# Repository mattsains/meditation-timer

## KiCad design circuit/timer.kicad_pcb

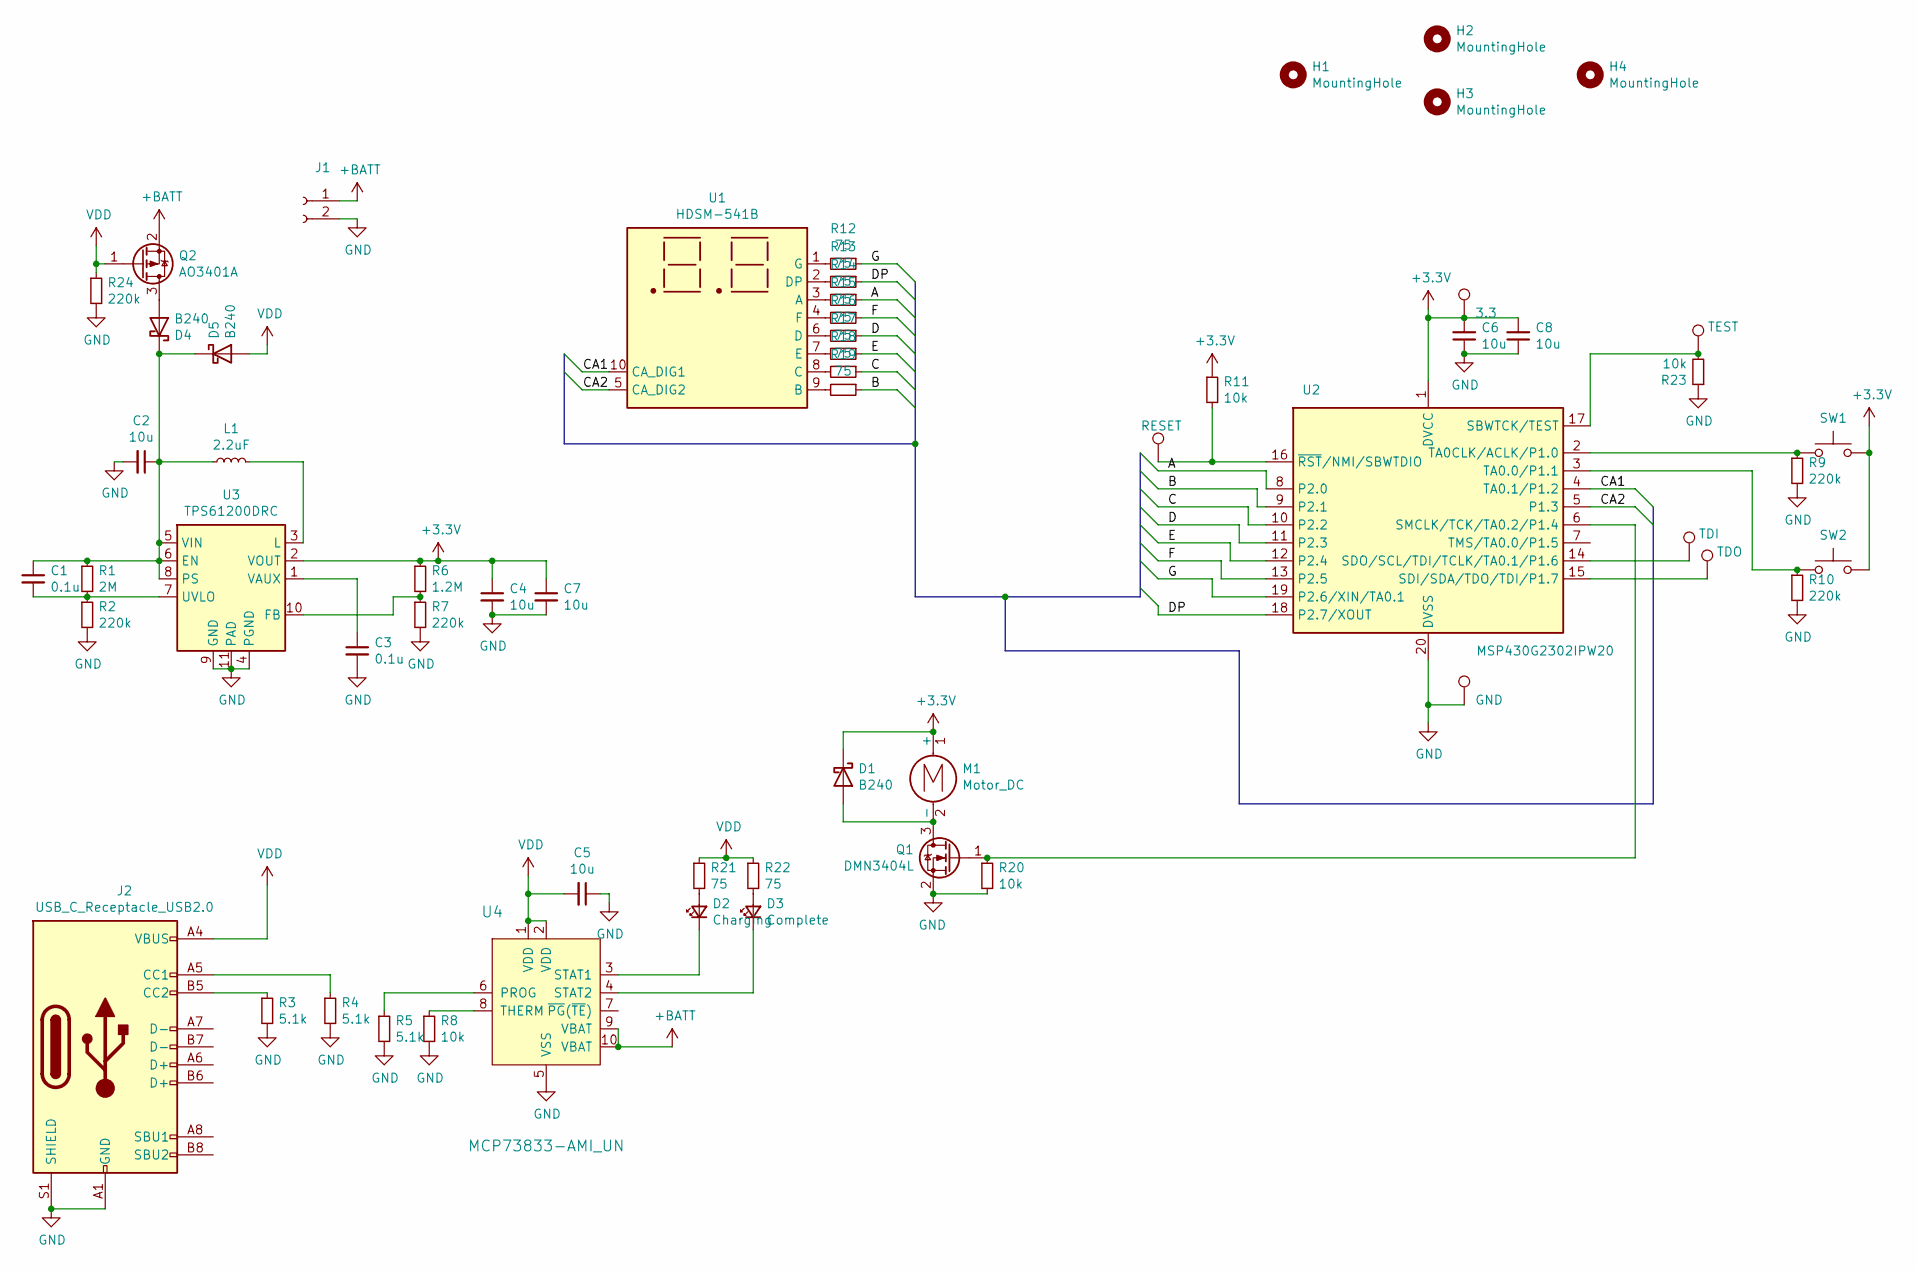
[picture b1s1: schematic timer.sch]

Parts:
C1, C3: 0.1u; C_0805_2012Metric
C2, C4, C5, C6, C7, C8: 10u; C_0805_2012Metric
D1, D4, D5: B240; D_SMB
D2: Charging; LED_0805_2012Metric
D3: Complete; LED_0805_2012Metric
H1, H2, H3, H4: MountingHole; MountingHole_4mm
J1: Conn_01x02_Female; JST_PH_B2B-PH-SM4-TB_1x02-1MP_P2.00mm_Vertical; LCSC C160352
J2: USB_C_Receptacle_USB2.0; USB_C_Receptacle_GCT_USB4085
L1: 2.2uF; L_Wuerth_WE-PD-Typ-7345
M1: Motor_DC; 2-wire-connector
Q1: DMN3404L; SOT-23
Q2: AO3401A; SOT-23
R1: 2M; R_0805_2012Metric
R2, R7, R9, R10, R24: 220k; R_0805_2012Metric
R3, R4, R5: 5.1k; R_0805_2012Metric
R6: 1.2M; R_0805_2012Metric
R8, R11, R20, R23: 10k; R_0805_2012Metric
R12, R13, R14, R15, R16, R17, R18, R19, R21, R22: 75; R_0805_2012Metric
SW1, SW2: SW_Push; SW_SPST_EVQP7A; LCSC C79167
TP1: RESET; TestPoint_Pad_D2.0mm
TP3: TDI; TestPoint_Pad_D2.0mm
TP4: TDO; TestPoint_Pad_D2.0mm
TP5: TEST; TestPoint_Pad_D2.0mm
TP6: GND; TestPoint_Pad_D2.0mm
TP7: 3.3; TestPoint_Pad_D2.0mm
U1: HDSM-541B; HDSM-441B_HDSM-443B-bigger
U2: MSP430G2302IPW20; TSSOP-20_4.4x6.5mm_P0.65mm
U3: TPS61200DRC; Texas_S-PVSON-N10_ThermalVias; LCSC C140320
U4: MCP73833-AMI_UN; MSOP-10_W3mm; MPN MCP73833-AMI/UN; Digi-Key_PN MCP73833-AMI/UN-ND

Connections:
+3V3: C4.1, C6.2, C7.1, C8.2, D1.1 (K), M1.1 (+), R6.1, R11.1, SW1.2, SW2.2, TP7.1, U2.1 (DVCC), U3.2 (VOUT)
/A: R14.1, U2.8 (P2.0)
/B: R19.1, U2.9 (P2.1)
/C: R18.1, U2.10 (P2.2)
/CA1: U1.10 (CA_DIG1), U2.4 (TA0.1/P1.2)
/CA2: U1.5 (CA_DIG2), U2.5 (P1.3)
/D: R16.1, U2.11 (P2.3)
/DP: R13.1, U2.18 (P2.7/XOUT)
/E: R17.1, U2.12 (P2.4)
/F: R15.1, U2.13 (P2.5)
/G: R12.1, U2.19 (P2.6/XIN/TA0.1)
GND: C2.2, C3.2, C4.2, C5.1, C6.1, C7.2, C8.1, J1.2, J2.A1 (GND), J2.A12 (GND), J2.B1 (GND), J2.B12 (GND), J2.S1 (SHIELD), Q1.2 (S), R2.2, R3.2, R4.2, R5.2, R7.2, R8.2, R9.2, R10.2, R20.2, R23.1, R24.2, TP6.1, U2.20 (DVSS), U3.4 (PGND), U3.9 (GND), U3.11 (PAD), U4.5 (VSS)
unnamed: C1.2, R1.2, R2.1, U3.7 (UVLO)
unnamed: C3.1, U3.1 (VAUX)
unnamed: D1.2 (A), M1.2 (-), Q1.3 (D)
unnamed: D2.1 (K), U4.3 (STAT1)
unnamed: D2.2 (A), R21.2
unnamed: D3.1 (K), U4.4 (STAT2)
unnamed: D3.2 (A), R22.2
unnamed: D4.2 (A), Q2.3 (D)
unnamed: J2.A5 (CC1), R4.1
unnamed: J2.B5 (CC2), R3.1
unnamed: L1.2, U3.3 (L)
unnamed: Q1.1 (G), R20.1, U2.6 (SMCLK/TCK/TA0.2/P1.4)
unnamed: R5.1, U4.6 (PROG)
unnamed: R6.2, R7.1, U3.10 (FB)
unnamed: R8.1, U4.8 (THERM)
unnamed: R9.1, SW1.1, U2.2 (TA0CLK/ACLK/P1.0)
unnamed: R10.1, SW2.1, U2.3 (TA0.0/P1.1)
unnamed: R11.2, TP1.1, U2.16 (~RST~/NMI/SBWTDIO)
unnamed: R12.2, U1.1 (G)
unnamed: R13.2, U1.2 (DP)
unnamed: R14.2, U1.3 (A)
unnamed: R15.2, U1.4 (F)
unnamed: R16.2, U1.6 (D)
unnamed: R17.2, U1.7 (E)
unnamed: R18.2, U1.8 (C)
unnamed: R19.2, U1.9 (B)
unnamed: R23.2, TP5.1, U2.17 (SBWTCK/TEST)
unnamed: TP3.1, U2.14 (SDO/SCL/TDI/TCLK/TA0.1/P1.6)
unnamed: TP4.1, U2.15 (SDI/SDA/TDO/TDI/P1.7)
VDD: C5.2, D5.2 (A), J2.A4 (VBUS), J2.A9 (VBUS), J2.B4 (VBUS), J2.B9 (VBUS), Q2.1 (G), R21.1, R22.1, R24.1, U4.1 (VDD), U4.2 (VDD)

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
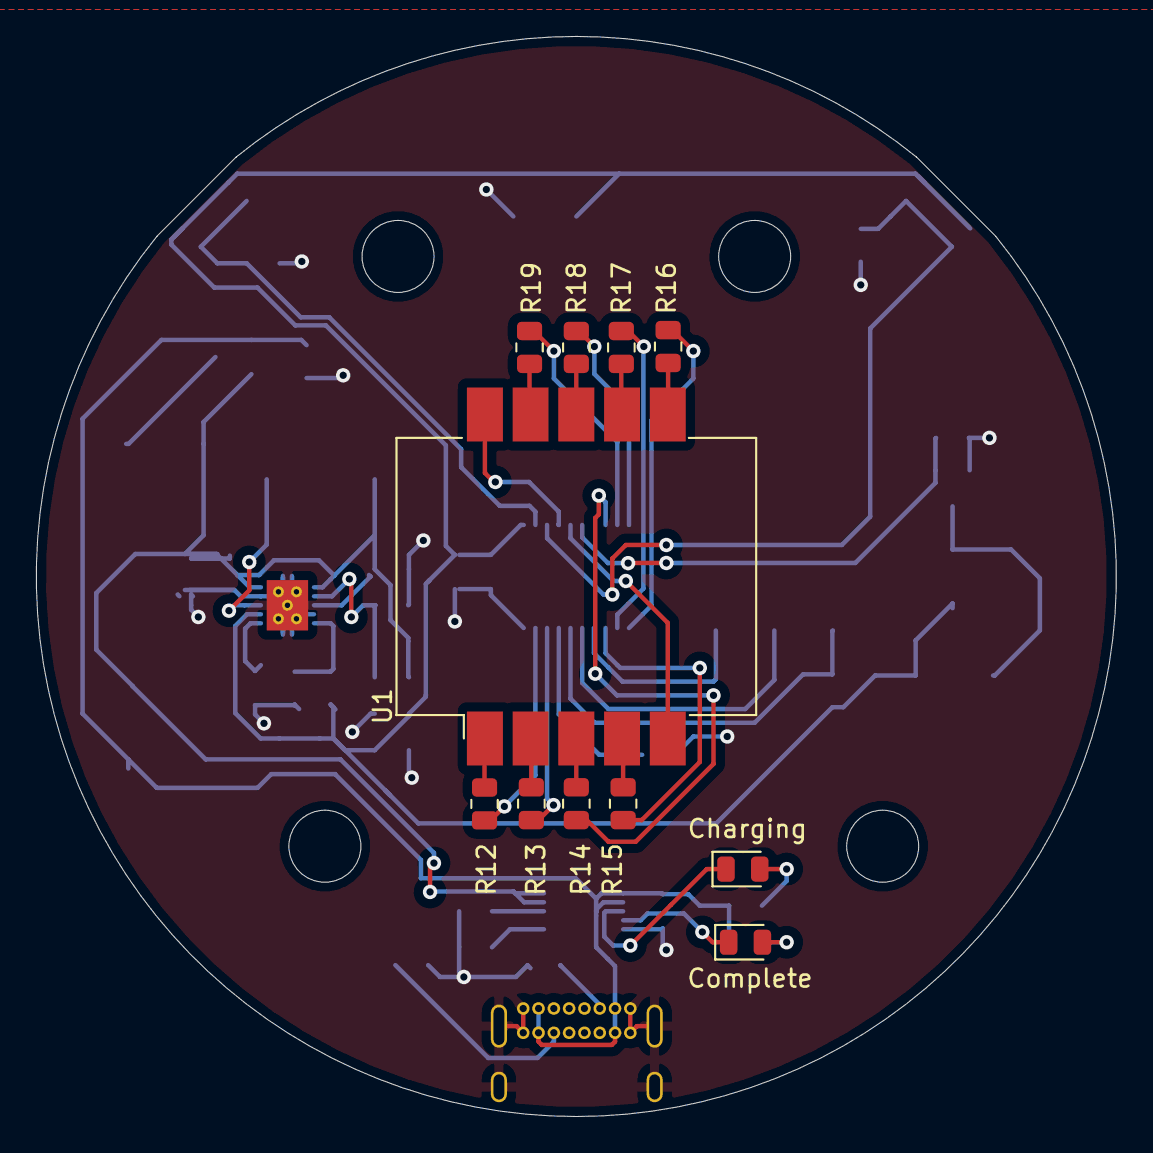
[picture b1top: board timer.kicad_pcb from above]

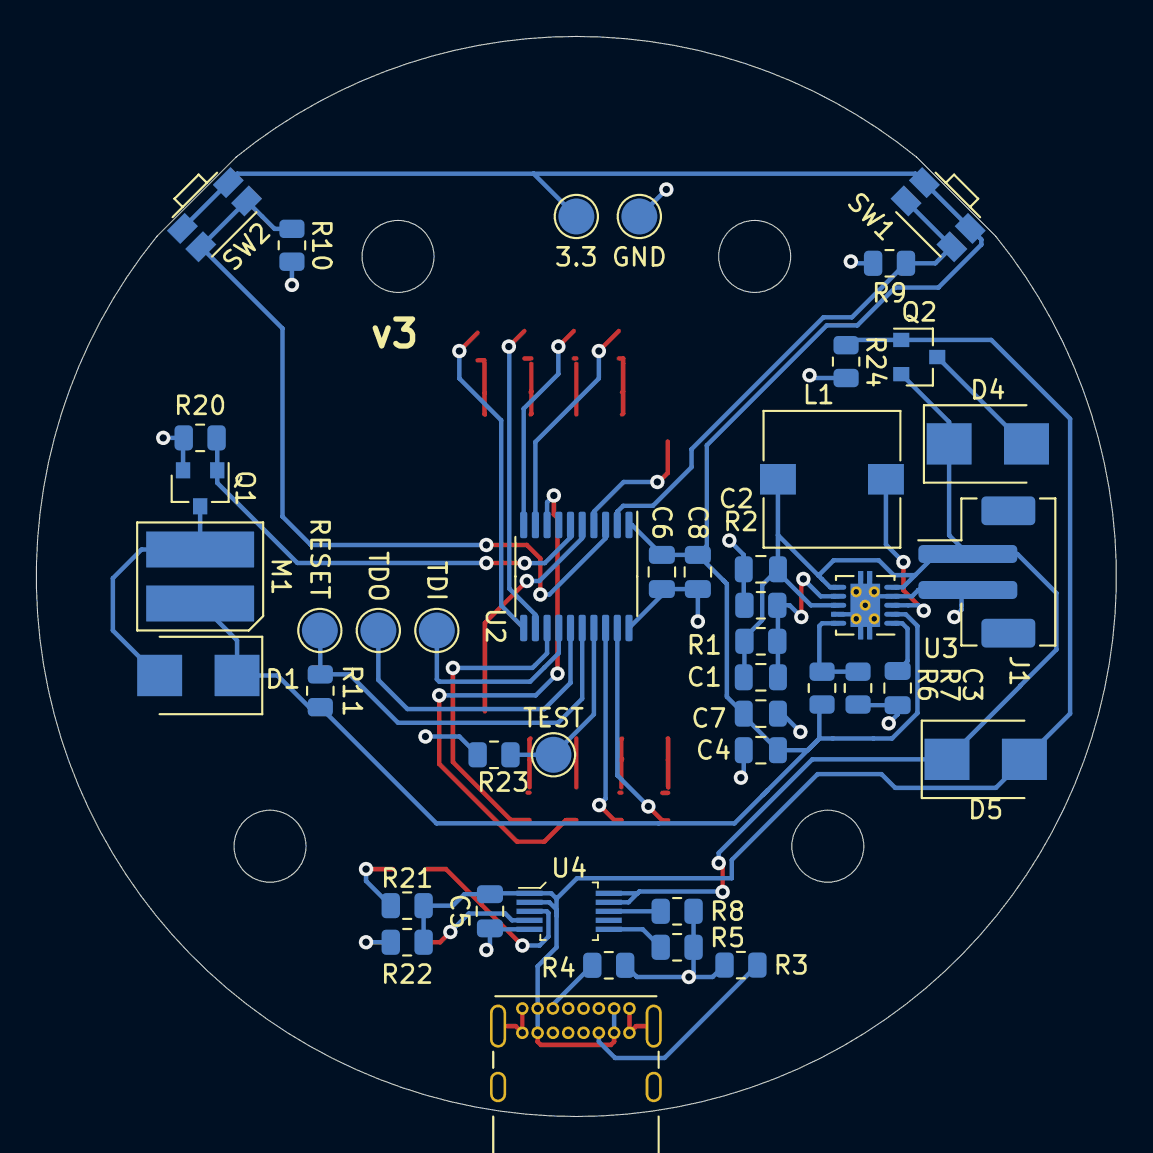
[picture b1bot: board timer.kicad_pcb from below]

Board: 2 copper layers, 60.0 x 60.0 mm, 59 parts (44 on the bottom side), 43 nets.

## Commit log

2021-06-08 v3 and coding complete
2021-06-09 ready for manufacture
